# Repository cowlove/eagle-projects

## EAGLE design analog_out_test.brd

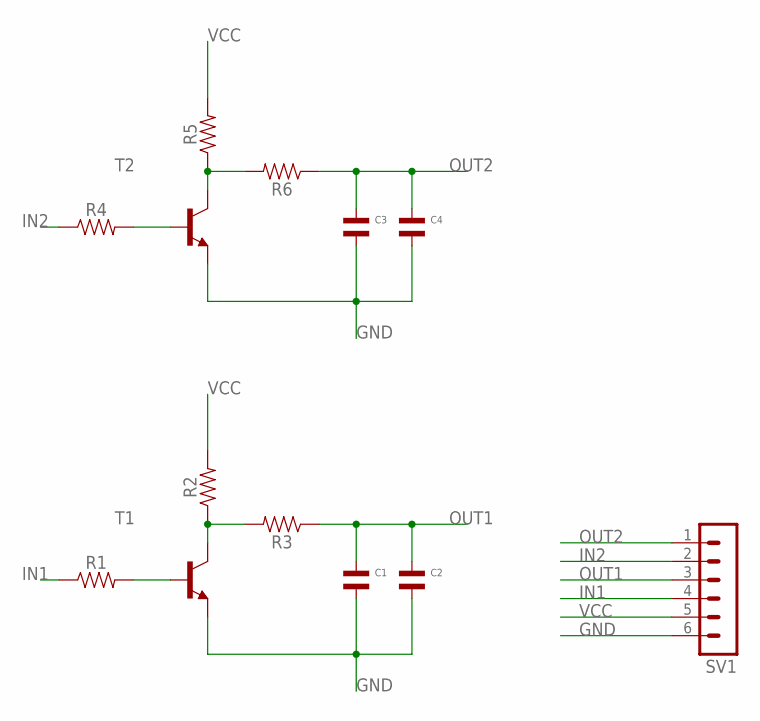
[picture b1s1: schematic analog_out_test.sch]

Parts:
C1, C2, C3, C4: CAPACITOR_NP_1206; C1206
R1, R2, R3, R4, R5, R6: 1206
SV1: MA06-1
T1, T2: BC849-NPN-SOT23-BEC; SOT23-BEC

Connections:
GND: C1.P$2, C2.P$2, C3.P$2, C4.P$2, SV1.6, T1.E, T2.E
IN1: R1.1, SV1.4
IN2: R4.1, SV1.2
unnamed: R2.1, R3.2, T1.C
unnamed: R1.2, T1.B
unnamed: R4.2, T2.B
unnamed: R5.1, R6.2, T2.C
OUT1: C1.P$1, C2.P$1, R3.1, SV1.3
OUT2: C3.P$1, C4.P$1, R6.1, SV1.1
VCC: R2.2, R5.2, SV1.5

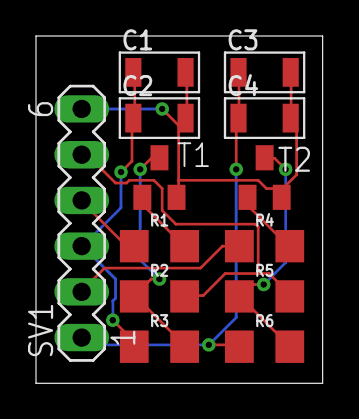
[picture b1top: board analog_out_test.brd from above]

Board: 2 copper layers, 15.9 x 19.3 mm, 13 parts (0 on the bottom side), 10 nets.

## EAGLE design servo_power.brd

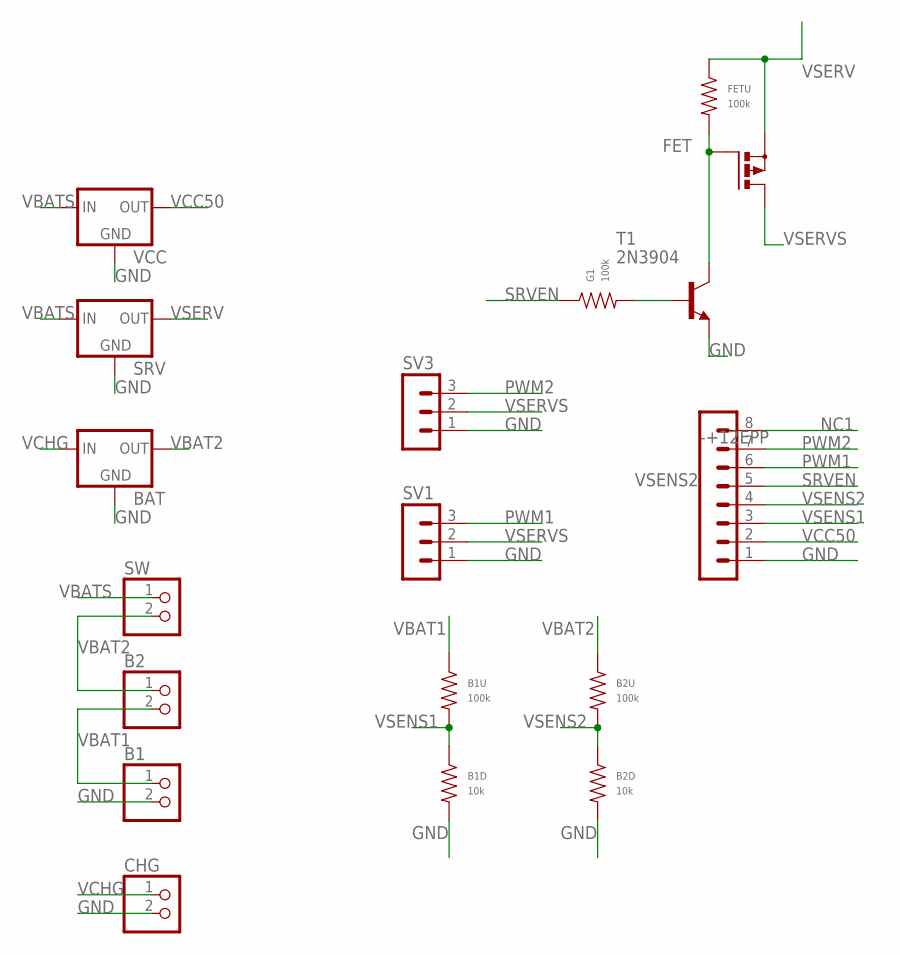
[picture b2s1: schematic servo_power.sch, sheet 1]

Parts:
-+12EPP: MA08-1
B1, B2: PINHD-1X2; 1X02
B1D, B2D: 10k; R1206
B1U, B2U: 100k; R1206
BAT: 78XXS
CHG: PINHD-1X2; 1X02
FET: PMOSFET_PTO220BV; TO220BV
FETU: 100k; R1206
G1: 100k; R1206
SRV: 78XXS
SV1, SV3: MA03-1
SW: PINHD-1X2; 1X02
T1: 2N3904; TO92
VCC: 78XXS

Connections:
GND: -+12EPP.1, B1.2, B1D.P$2, B2D.P$2, BAT.GND, CHG.2, SRV.GND, SV1.1, SV3.1, T1.3 (E), VCC.GND
unnamed: G1.P$2, T1.2 (B)
unnamed: FET.G, FETU.P$2, T1.1 (C)
NC1: -+12EPP.8
PWM1: -+12EPP.6, SV1.3
PWM2: -+12EPP.7, SV3.3
SRVEN: -+12EPP.5, G1.P$1
VBAT1: B1.1, B1U.P$1, B2.2
VBAT2: B2.1, B2U.P$1, BAT.OUT, SW.2
VBATS: SRV.IN, SW.1, VCC.IN
VCC50: -+12EPP.2, VCC.OUT
VCHG: BAT.IN, CHG.1
VSENS1: -+12EPP.3, B1D.P$1, B1U.P$2
VSENS2: -+12EPP.4, B2D.P$1, B2U.P$2
VSERV: FET.S, FETU.P$1, SRV.OUT
VSERVS: FET.D, SV1.2, SV3.2

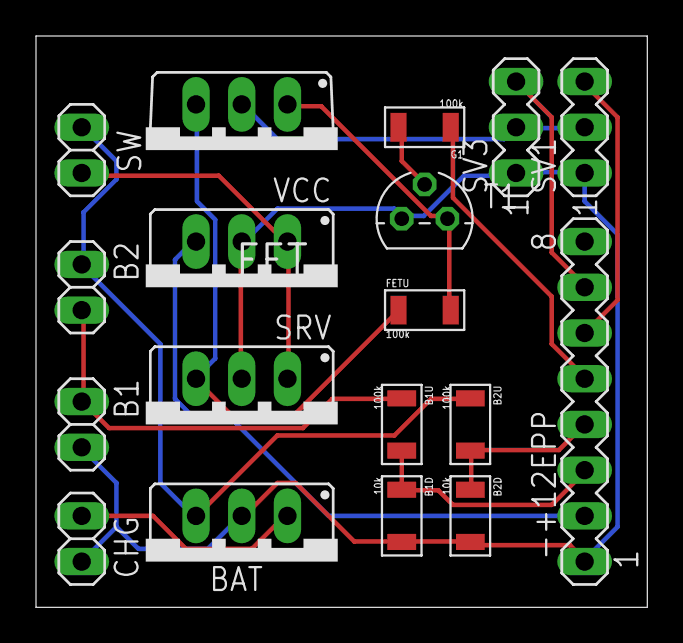
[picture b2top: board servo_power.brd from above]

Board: 2 copper layers, 34.0 x 31.7 mm, 18 parts (0 on the bottom side), 15 nets.

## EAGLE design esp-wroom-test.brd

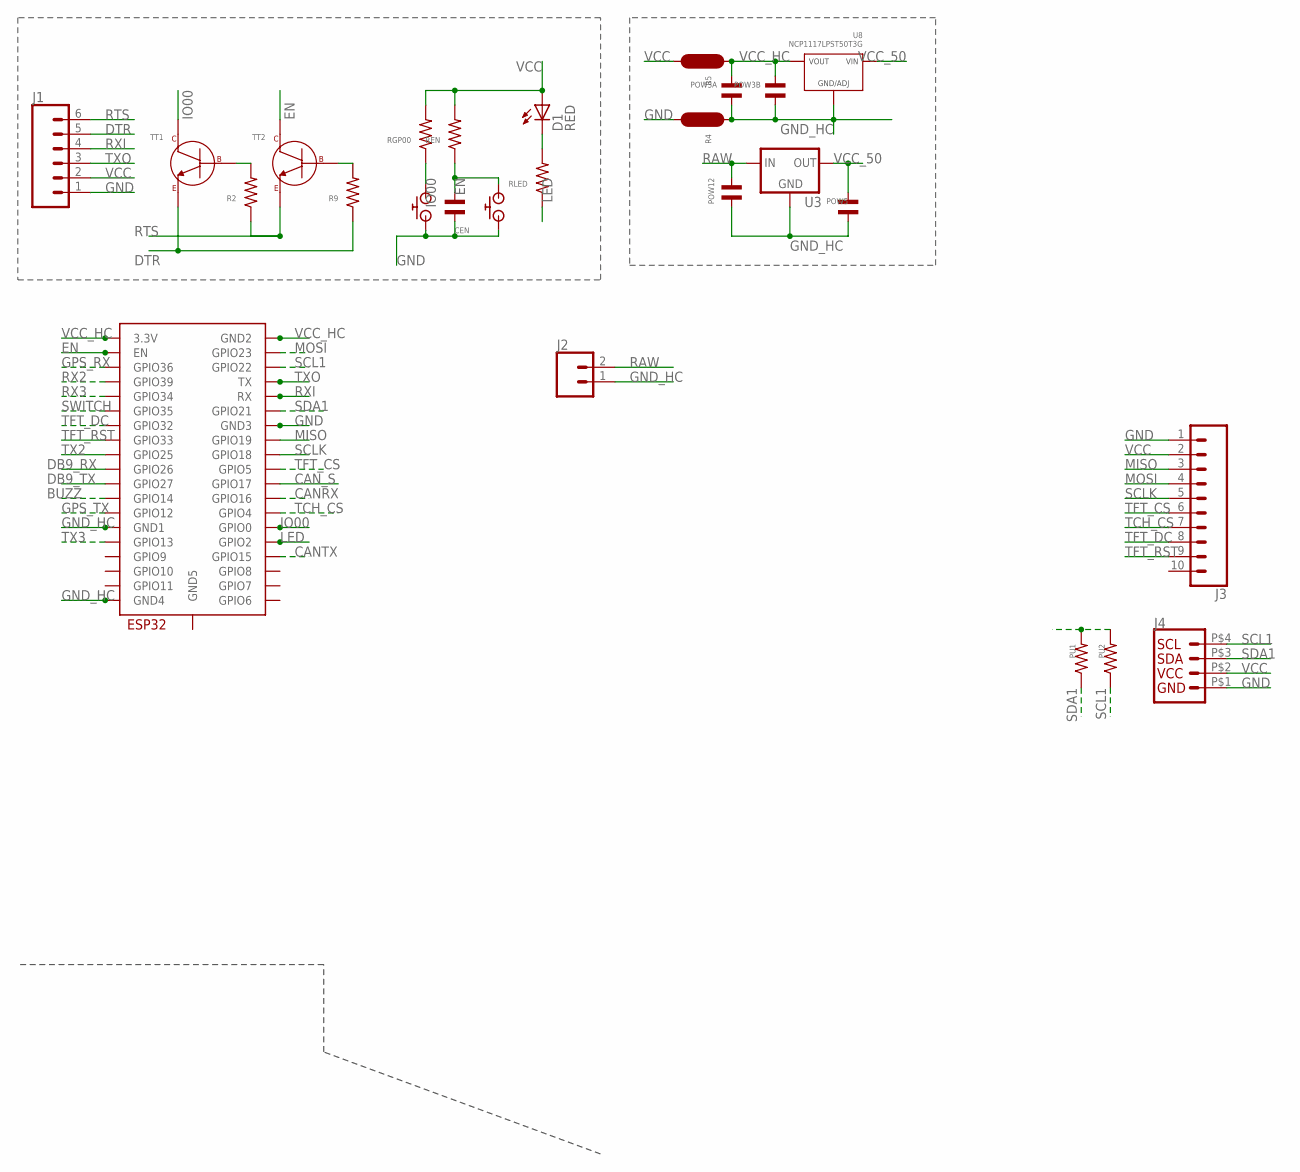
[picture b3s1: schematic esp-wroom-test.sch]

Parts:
CEN: CAPACITOR_NP_1206; C1206
D1: RED; LED-1206
J1: CONN_06; 1X6-1.25MM-SMD
J2: CONN_02; 1X02
J3: CONN_10; 1X10-1.25MM
J4: Vertical Qwiic Connector; JST04_1MM_HOLES
POW3A, POW3B, POW5, POW12: CAPACITOR_NP_1206; C1206
PU1, PU2: RESISTOR_1206; R1206
R2, R9: RESISTOR_1206; R1206
R4, R5: JUMPER; R0603_JMP
REN: RESISTOR_1206; R1206
RGP00: RESISTOR_1206; R1206
RLED: RESISTOR_1206; R1206
SW1, SW2: AMAZON_BUTTONB2010; C2010
TT1, TT2: MF-DSC-SOT233-MMBT3904; SOT-23-3
U3: V_REG_78XXSINK; TO220-IGO
U8: NCP1117LPST50T3G; SOT-223-3
U$3: ESP32-WROOM

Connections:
BUZZ: U$3.IO14 (GPIO14)
CANRX: U$3.IO16 (GPIO16)
CANTX: U$3.IO15 (GPIO15)
CAN_S: U$3.IO17 (GPIO17)
DB9_RX: U$3.IO26 (GPIO26)
DB9_TX: U$3.IO27 (GPIO27)
DTR: J1.5, R9.P$1, TT1.P$2 (EMITTER)
EN: CEN.P$1, REN.P$1, SW1.P$1, TT2.P$3 (COLLECTOR), U$3.EN
GND: CEN.P$2, J1.1, J3.1, J4.P$1 (1), R4.P$2, SW1.P$2, SW2.P$2, U$3.GND3
GND_HC: J2.1, POW3A.P$2, POW3B.P$2, POW5.P$2, POW12.P$2, R4.P$1, U3.GND, U8.P$2 (GND/ADJ), U$3.GND1, U$3.GND4
GPS_RX: U$3.SENSOR_VP (GPIO36)
GPS_TX: U$3.IO12 (GPIO12)
IO00: RGP00.P$1, SW2.P$1, TT1.P$3 (COLLECTOR), U$3.IO0 (GPIO0)
LED: RLED.P$1, U$3.IO2 (GPIO2)
MISO: J3.3, U$3.IO19 (GPIO19)
MOSI: J3.4, U$3.IO23 (GPIO23)
unnamed: D1.C, RLED.P$2
unnamed: R2.P$2, TT1.P$1 (BASE)
unnamed: R9.P$2, TT2.P$1 (BASE)
RAW: J2.2, POW12.P$1, U3.IN
RTS: J1.6, R2.P$1, TT2.P$2 (EMITTER)
RX2: U$3.SENSOR_VN (GPIO39)
RX3: U$3.IO34 (GPIO34)
RXI: J1.4, U$3.RX
SCL1: J4.P$4 (4), PU2.P$1, U$3.IO22 (GPIO22)
SCLK: J3.5, U$3.IO18 (GPIO18)
SDA1: J4.P$3 (3), PU1.P$1, U$3.IO21 (GPIO21)
SWITCH: U$3.IO35 (GPIO35)
TCH_CS: J3.7, U$3.IO4 (GPIO4)
TFT_CS: J3.6, U$3.IO5 (GPIO5)
TFT_DC: J3.8, U$3.IO32 (GPIO32)
TFT_RST: J3.9, U$3.IO33 (GPIO33)
TX2: U$3.IO25 (GPIO25)
TX3: U$3.IO13 (GPIO13)
TXO: J1.3, U$3.TX
VCC: D1.A, J1.2, J3.2, J4.P$2 (2), PU1.P$2, PU2.P$2, R5.P$2, REN.P$2, RGP00.P$2
VCC_50: POW5.P$1, U3.OUT, U8.P$4 (VIN)
VCC_HC: POW3A.P$1, POW3B.P$1, R5.P$1, U8.P$1 (VOUT), U8.P$3 (VOUT), U$3.3V3 (3.3V), U$3.GND2

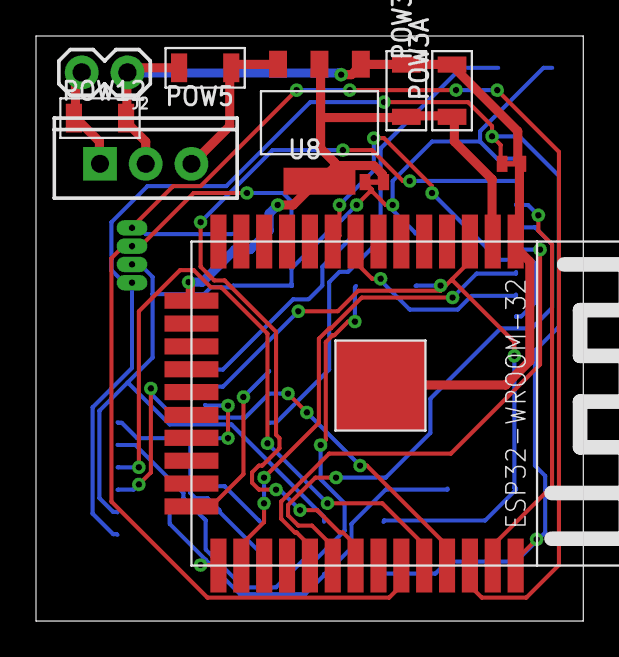
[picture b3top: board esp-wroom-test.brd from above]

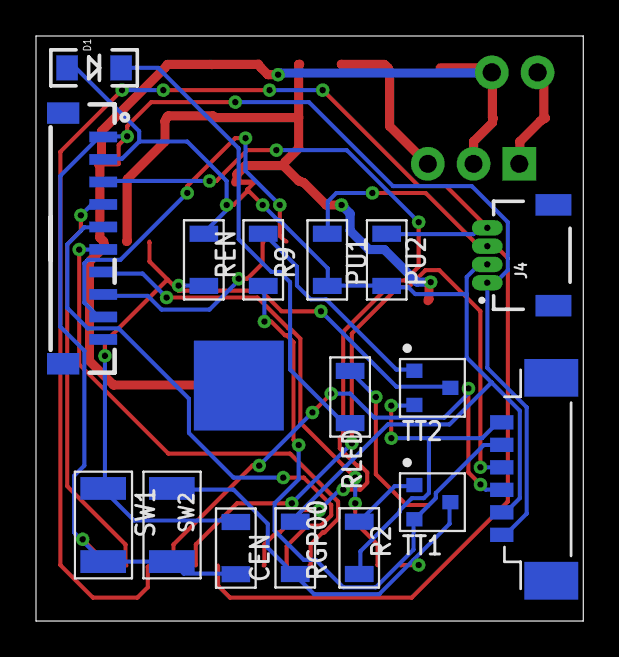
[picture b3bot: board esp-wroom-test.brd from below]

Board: 2 copper layers, 30.4 x 32.5 mm, 26 parts (16 on the bottom side), 25 nets.

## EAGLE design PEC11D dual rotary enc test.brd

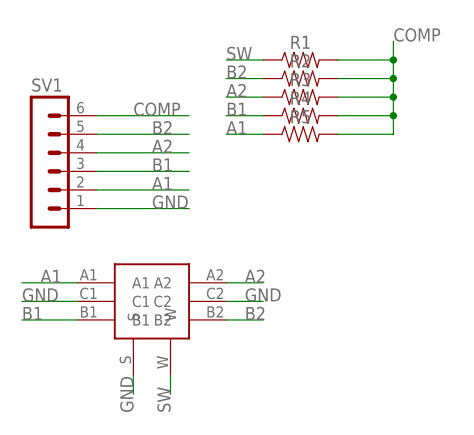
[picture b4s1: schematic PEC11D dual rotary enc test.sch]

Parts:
R1, R2, R3, R4, R5: 1206
SV1: MA06-1
U$1: PEC11DPEC11D; PEC11D_TH

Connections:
A1: R5.1, SV1.2, U$1.A1
A2: R3.1, SV1.4, U$1.A2
B1: R4.1, SV1.3, U$1.B1
B2: R2.1, SV1.5, U$1.B2
COMP: R1.2, R2.2, R3.2, R4.2, R5.2, SV1.6
GND: SV1.1, U$1.C1, U$1.C2, U$1.S
SW: R1.1, U$1.W

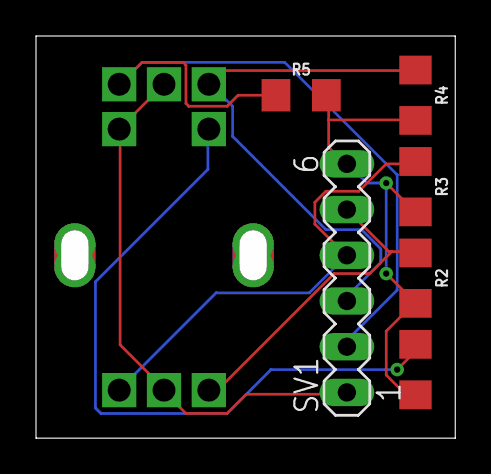
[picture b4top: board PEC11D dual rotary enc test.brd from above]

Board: 2 copper layers, 21.8 x 20.8 mm, 7 parts (0 on the bottom side), 7 nets.

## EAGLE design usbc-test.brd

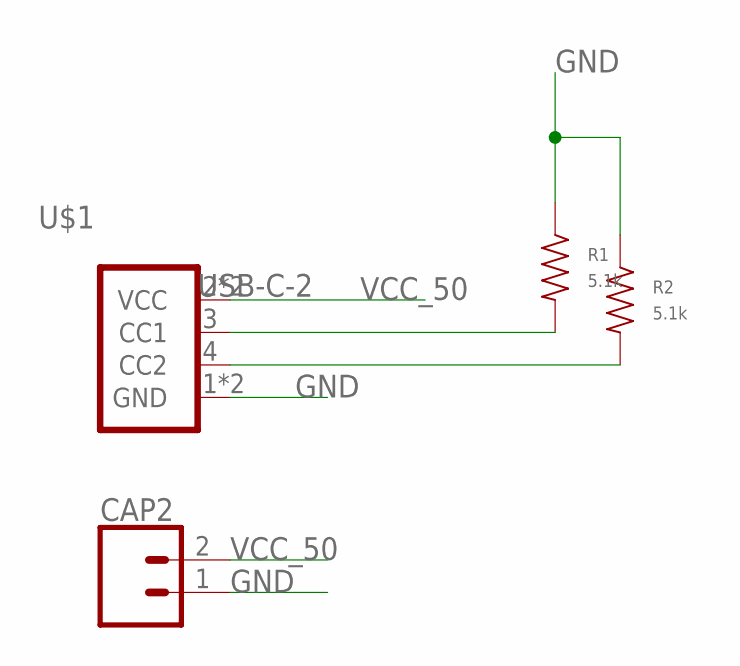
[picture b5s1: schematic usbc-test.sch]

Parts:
CAP2: CONN_02; 1X02
R1, R2: 5.1k; R0603
U$1: USB-C-2; USB-C-16

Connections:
GND: CAP2.1, R1.P$1, R2.P$1, U$1.1 (GND), U$1.6 (GND)
unnamed: R1.P$2, U$1.3 (CC1)
unnamed: R2.P$2, U$1.4 (CC2)
VCC_50: CAP2.2, U$1.2 (VCC), U$1.5 (VCC)

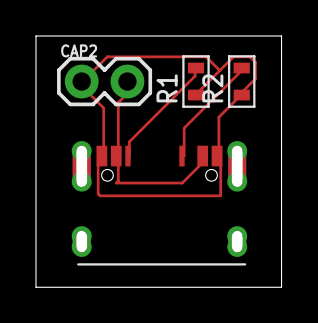
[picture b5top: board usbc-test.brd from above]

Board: 2 copper layers, 13.0 x 13.4 mm, 4 parts (0 on the bottom side), 4 nets.

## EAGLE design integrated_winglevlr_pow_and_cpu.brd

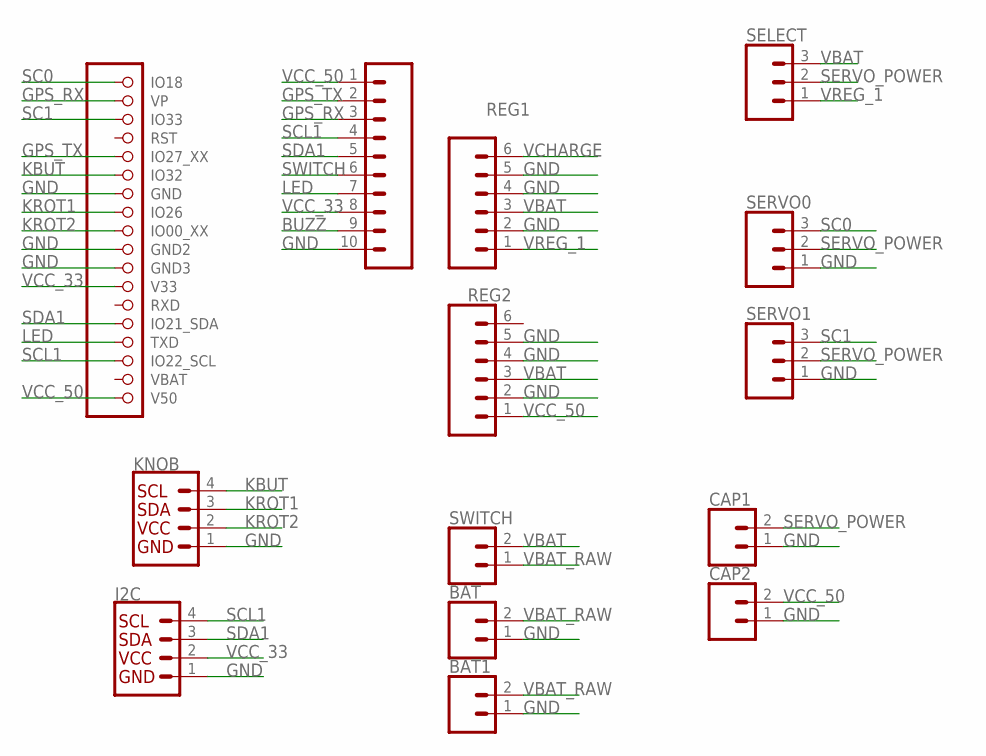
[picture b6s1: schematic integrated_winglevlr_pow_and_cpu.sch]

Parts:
BAT, BAT1: CONN_02; 1X02
CAP1, CAP2: CONN_02; 1X02
I2C: Vertical Qwiic Connector; JST04_1MM_VERT
J2: CONN_10; 1X10-1.25MM
JP1: 000_ESP32_D1MINI; 00_2X9
KNOB: Vertical Qwiic Connector; JST04_1MM_VERT
REG1, REG2: CONN_06SILK_FEMALE_PTH; 1X06
SELECT: 455-1750-1-ND; 1X03
SERVO0, SERVO1: 455-1750-1-ND; 1X03
SWITCH: CONN_02; 1X02

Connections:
BUZZ: J2.9
GND: BAT.1, BAT1.1, CAP1.1, CAP2.1, I2C.1, J2.10, JP1.7 (GND), JP1.10 (GND2), JP1.11 (GND3), KNOB.1, REG1.2, REG1.4, REG1.5, REG2.2, REG2.4, REG2.5, SERVO0.1, SERVO1.1
GPS_RX: J2.3, JP1.2 (VP)
GPS_TX: J2.2, JP1.5 (IO27_XX)
KBUT: JP1.6 (IO32), KNOB.4
KROT1: JP1.8 (IO26), KNOB.3
KROT2: JP1.9 (IO00_XX), KNOB.2
LED: J2.7, JP1.15 (TXD)
SC0: JP1.1 (IO18), SERVO0.3
SC1: JP1.3 (IO33), SERVO1.3
SCL1: I2C.4, J2.4, JP1.16 (IO22_SCL)
SDA1: I2C.3, J2.5, JP1.14 (IO21_SDA)
SERVO_POWER: CAP1.2, SELECT.2, SERVO0.2, SERVO1.2
SWITCH: J2.6
VBAT: REG1.3, REG2.3, SELECT.3, SWITCH.2
VBAT_RAW: BAT.2, BAT1.2, SWITCH.1
VCC_33: I2C.2, J2.8, JP1.12 (V33)
VCC_50: CAP2.2, J2.1, JP1.18 (V50), REG2.1
VCHARGE: REG1.6
VREG_1: REG1.1, SELECT.1

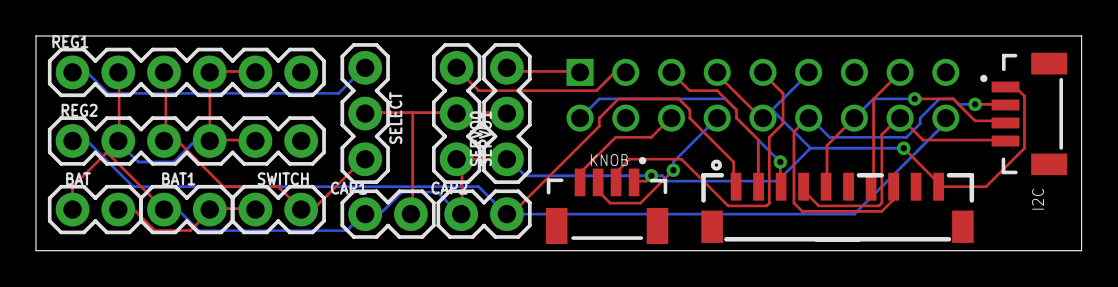
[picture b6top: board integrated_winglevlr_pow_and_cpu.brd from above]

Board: 2 copper layers, 58.1 x 11.9 mm, 14 parts (1 on the bottom side), 17 nets.

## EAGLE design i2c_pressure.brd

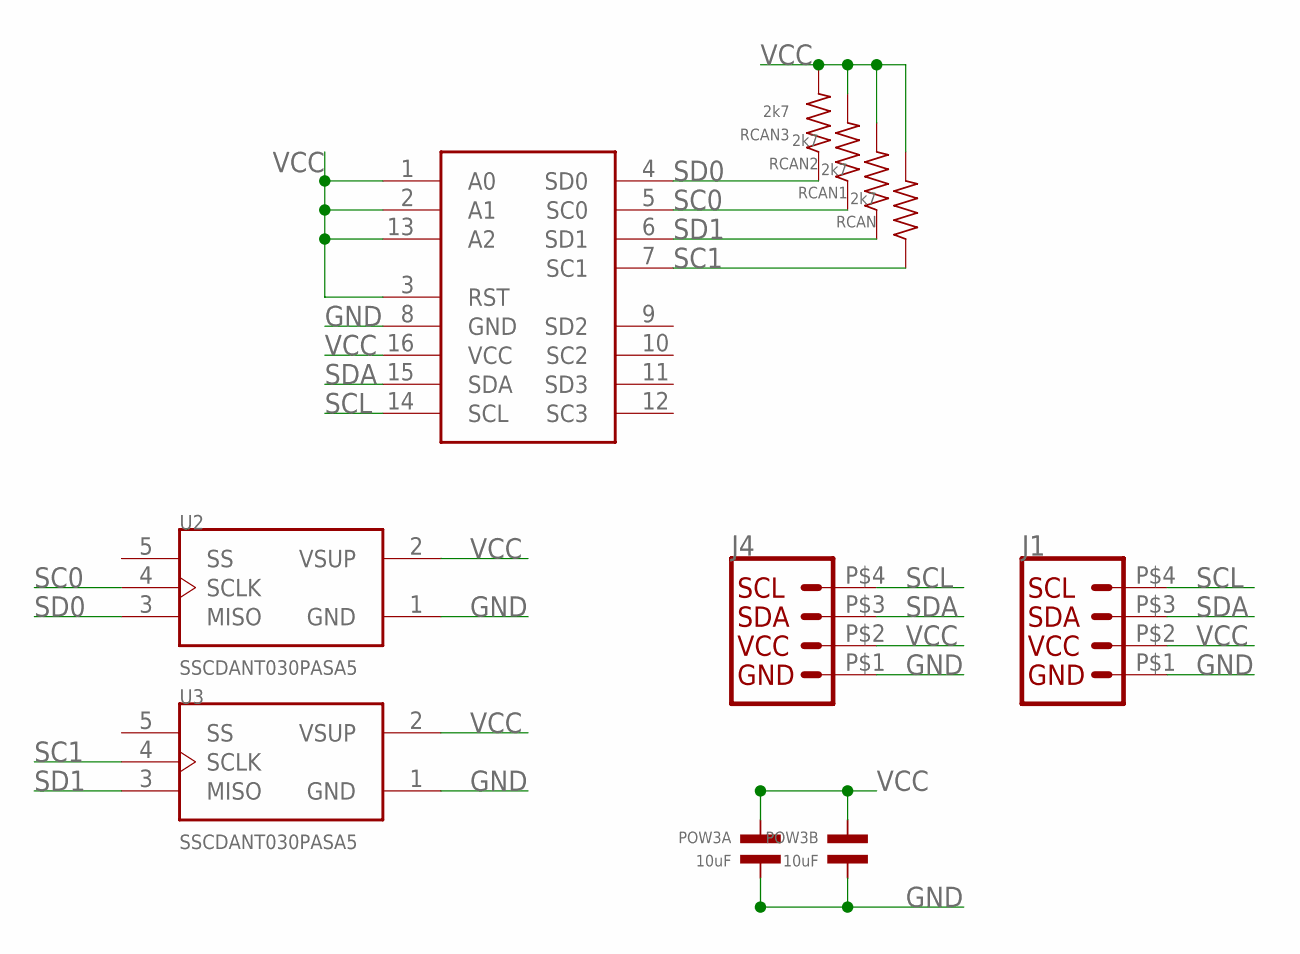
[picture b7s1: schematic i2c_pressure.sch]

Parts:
J1, J4: Vertical Qwiic Connector; JST04_1MM_HOLES
POW3A, POW3B: 10uF; C0603
RCAN, RCAN1, RCAN2, RCAN3: 2k7; R0603
U2, U3: SSCDANT030PASA5; XDCR_SSCDANT030PASA5
U$1: TCA9546ATSSOP16; TSSOP16

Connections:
GND: J1.P$1 (1), J4.P$1 (1), POW3A.P$2, POW3B.P$2, U2.1 (GND), U3.1 (GND), U$1.8 (GND)
SC0: RCAN2.P$1, U2.4 (SCLK), U$1.5 (SC0)
SC1: RCAN.P$1, U3.4 (SCLK), U$1.7 (SC1)
SCL: J1.P$4 (4), J4.P$4 (4), U$1.14 (SCL)
SD0: RCAN3.P$1, U2.3 (MISO), U$1.4 (SD0)
SD1: RCAN1.P$1, U3.3 (MISO), U$1.6 (SD1)
SDA: J1.P$3 (3), J4.P$3 (3), U$1.15 (SDA)
VCC: J1.P$2 (2), J4.P$2 (2), POW3A.P$1, POW3B.P$1, RCAN.P$2, RCAN1.P$2, RCAN2.P$2, RCAN3.P$2, U2.2 (VSUP), U3.2 (VSUP), U$1.1 (A0), U$1.2 (A1), U$1.3 (RST), U$1.13 (A2), U$1.16 (VCC)

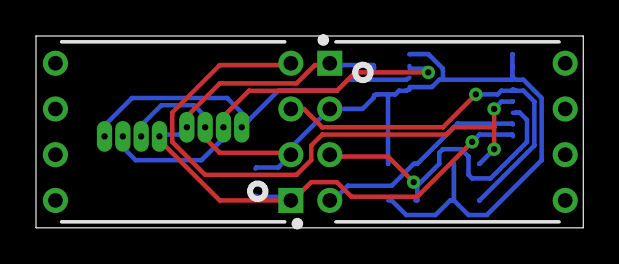
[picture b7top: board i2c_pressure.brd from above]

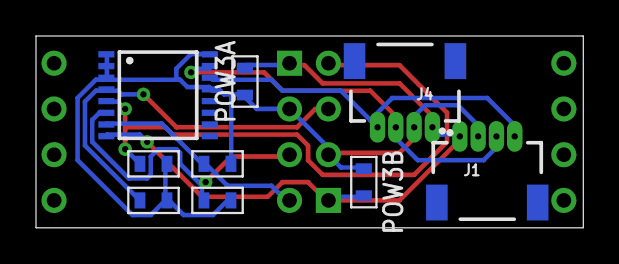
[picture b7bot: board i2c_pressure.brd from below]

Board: 2 copper layers, 30.4 x 10.7 mm, 11 parts (9 on the bottom side), 8 nets.

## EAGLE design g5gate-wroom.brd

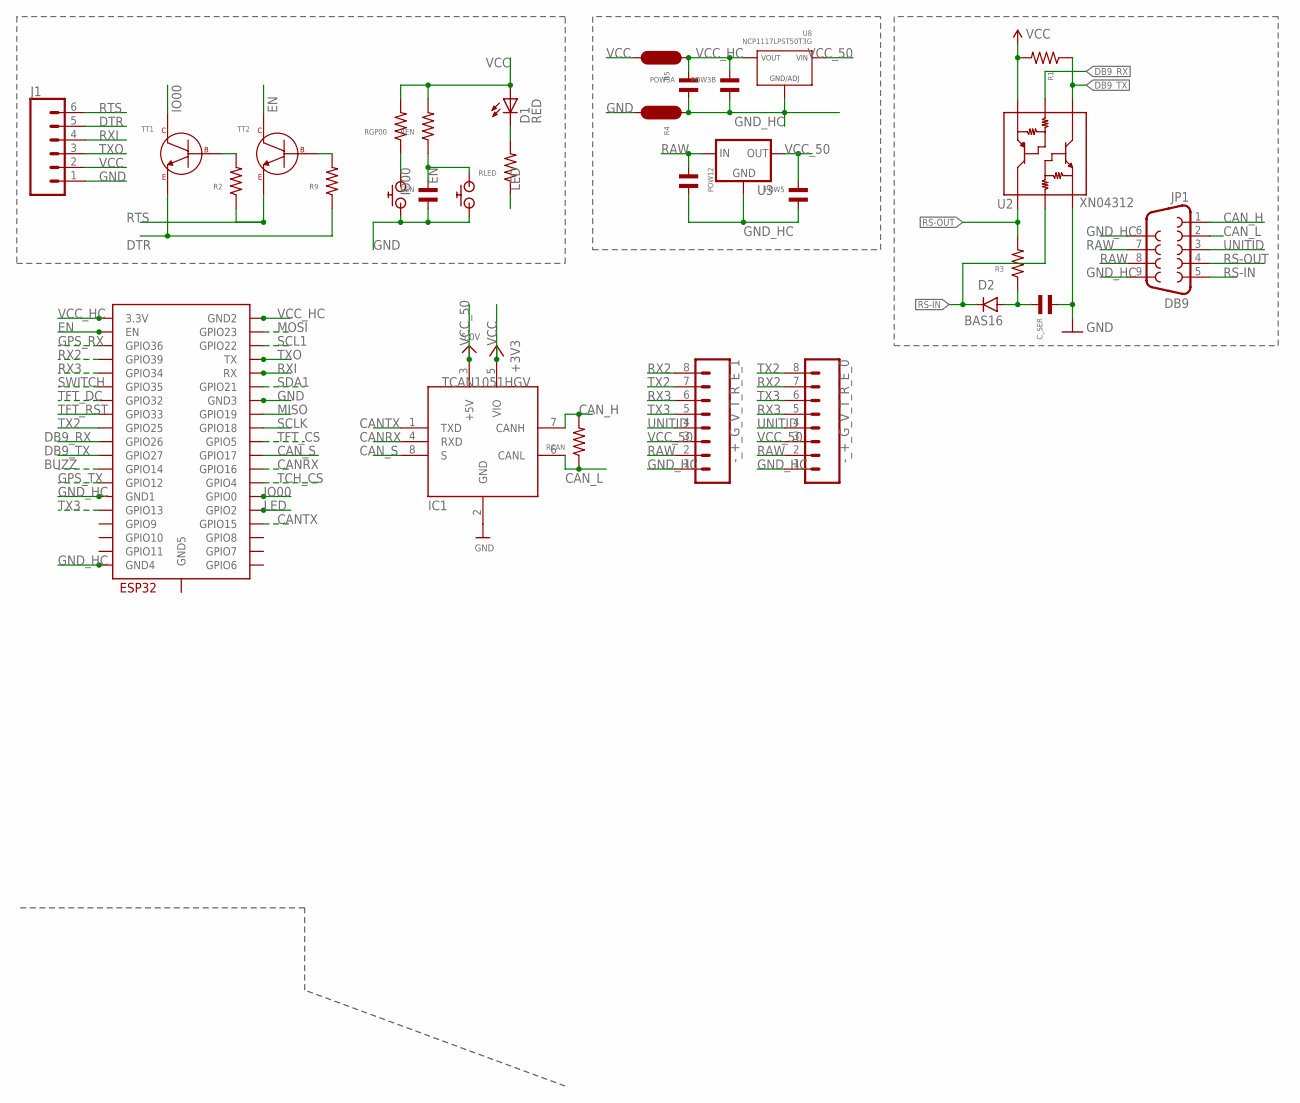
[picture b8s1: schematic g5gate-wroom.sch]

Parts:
-_+_G_V_T_R_E_0, -_+_G_V_T_R_E_1: MF-CON-2.54mm-01x08; 1X08
CEN: CAPACITOR_NP_0603; C0603
C_SER: CAPACITOR_NP_0603; C0603
D1: RED; LED-0603
D2: BAS16; SOD-323
IC1: TCAN1051HGV; SOIC8_150MIL
J1: CONN_06; 1X6-1.25MM-SMD
JP1: DB9
POW3A, POW3B, POW5, POW12: CAPACITOR_NP_0603; C0603
R1, R2, R3, R9: RESISTOR_0603; R0603
R4, R5: JUMPER; R0603_JMP
RCAN: RESISTOR_0603; R0603
REN: RESISTOR_0603; R0603
RGP00: RESISTOR_0603; R0603
RLED: RESISTOR_0603; R0603
TT1, TT2: MF-DSC-SOT233-MMBT3904; SOT-23-3
U2: XN04312; SOT23-6
U3: V_REG_78XXSINK; TO220-IGO
U8: NCP1117LPST50T3G; SOT-223-3
U$1, U$2: AMAZON_BUTTONB2010; C2010
U$3: ESP32-WROOM

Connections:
BUZZ: U$3.IO14 (GPIO14)
CANRX: IC1.4 (RXD), U$3.IO16 (GPIO16)
CANTX: IC1.1 (TXD), U$3.IO15 (GPIO15)
CAN_H: IC1.7 (CANH), JP1.1, RCAN.P$2
CAN_L: IC1.6 (CANL), JP1.2, RCAN.P$1
CAN_S: IC1.8 (S), U$3.IO17 (GPIO17)
DB9_RX: U2.2 (B2), U$3.IO26 (GPIO26)
DB9_TX: R1.P$1, U2.1 (C1), U$3.IO27 (GPIO27)
DTR: J1.5, R9.P$1, TT1.P$2 (EMITTER)
EN: CEN.P$1, REN.P$1, TT2.P$3 (COLLECTOR), U$2.P$1, U$3.EN
GND: CEN.P$2, C_SER.P$2, IC1.2 (GND), J1.1, R4.P$2, U2.6 (E1), U$1.P$2, U$2.P$2, U$3.GND3
GND_HC: -_+_G_V_T_R_E_0.1, -_+_G_V_T_R_E_1.1, JP1.6, JP1.9, POW3A.P$2, POW3B.P$2, POW5.P$2, POW12.P$2, R4.P$1, U3.GND, U8.P$2 (GND/ADJ), U$3.GND1, U$3.GND4
GPS_RX: U$3.SENSOR_VP (GPIO36)
GPS_TX: U$3.IO12 (GPIO12)
IO00: RGP00.P$1, TT1.P$3 (COLLECTOR), U$1.P$1, U$3.IO0 (GPIO0)
LED: RLED.P$1, U$3.IO2 (GPIO2)
MISO: U$3.IO19 (GPIO19)
MOSI: U$3.IO23 (GPIO23)
unnamed: D1.C, RLED.P$2
unnamed: R2.P$2, TT1.P$1 (BASE)
unnamed: C_SER.P$1, D2.A, R3.P$1
unnamed: R9.P$2, TT2.P$1 (BASE)
RAW: -_+_G_V_T_R_E_0.2, -_+_G_V_T_R_E_1.2, JP1.7, JP1.8, POW12.P$1, U3.IN
RS-IN: D2.C, JP1.5, U2.5 (B1)
RS-OUT: JP1.4, R3.P$2, U2.4 (C2)
RTS: J1.6, R2.P$1, TT2.P$2 (EMITTER)
RX2: -_+_G_V_T_R_E_0.7, -_+_G_V_T_R_E_1.8, U$3.SENSOR_VN (GPIO39)
RX3: -_+_G_V_T_R_E_0.5, -_+_G_V_T_R_E_1.6, U$3.IO34 (GPIO34)
RXI: J1.4, U$3.RX
SCL1: U$3.IO22 (GPIO22)
SCLK: U$3.IO18 (GPIO18)
SDA1: U$3.IO21 (GPIO21)
SWITCH: U$3.IO35 (GPIO35)
TCH_CS: U$3.IO4 (GPIO4)
TFT_CS: U$3.IO5 (GPIO5)
TFT_DC: U$3.IO32 (GPIO32)
TFT_RST: U$3.IO33 (GPIO33)
TX2: -_+_G_V_T_R_E_0.8, -_+_G_V_T_R_E_1.7, U$3.IO25 (GPIO25)
TX3: -_+_G_V_T_R_E_0.6, -_+_G_V_T_R_E_1.5, U$3.IO13 (GPIO13)
TXO: J1.3, U$3.TX
UNITID: -_+_G_V_T_R_E_0.4, -_+_G_V_T_R_E_1.4, JP1.3
VCC: D1.A, IC1.5 (VIO), J1.2, R1.P$2, R5.P$2, REN.P$2, RGP00.P$2, U2.3 (E2)
VCC_50: -_+_G_V_T_R_E_0.3, -_+_G_V_T_R_E_1.3, IC1.3 (+5V), POW5.P$1, U3.OUT, U8.P$4 (VIN)
VCC_HC: POW3A.P$1, POW3B.P$1, R5.P$1, U8.P$1 (VOUT), U8.P$3 (VOUT), U$3.3V3 (3.3V), U$3.GND2

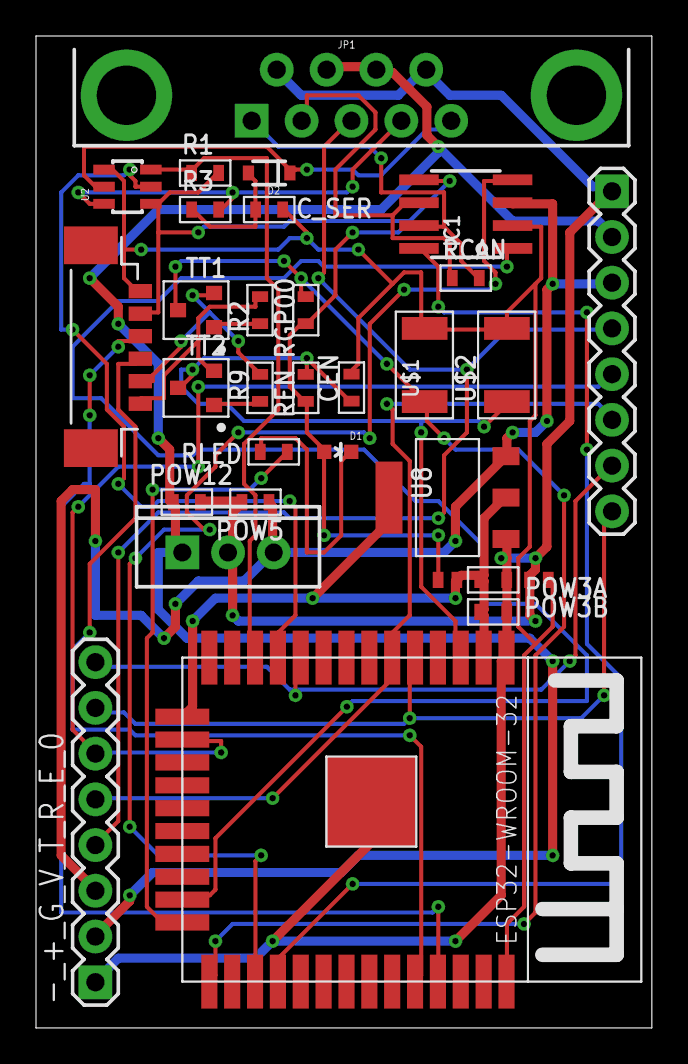
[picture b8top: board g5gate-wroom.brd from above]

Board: 2 copper layers, 34.2 x 55.1 mm, 31 parts (0 on the bottom side), 31 nets.

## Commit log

2021-03-03 Initial commit, TTGO-TS-dash-display ordered 3/2/2021, esp12e-test ordered 3/3
2021-03-04 Add button and STEMMA connectors to esp12e-test board
2021-03-06 Spin i2c_adc board, add jst connectors, 6 voltage divider channels
2021-03-16 First spin of TTGO to TFT mating board
2021-03-17 As ordered
2021-03-18 Added more trinkets to TFT touch boards
2021-03-18 Fix IO16 bug, change to better stemma-st connector
2021-03-18 Initial commit of wroom test board, as ordered
2021-03-18 Added tented vias
2021-03-19 Tinkering with expected changes for dash-mount board
2021-04-08 Ordered again
2021-04-08 Fix board bug, order again
2021-04-08 Enlarged usb pin holes
2021-04-11 Steerstick power and jst test boards, as ordered
2021-04-12 px4 board
2021-04-12 move via
2021-04-12 move other via
2021-04-13 Goddamit jst throughole test wasn't throughhole
2021-04-18 Fix USB connector dimensions
2021-04-26 Narrow board, add esp32 reset mechanism
2021-04-26 Actually save
2021-05-02 add 01jim.lbr
2021-05-02 add 00jim.lbr
2021-05-02 break out g5gate into wroom and min132 variands
2021-05-05 introduce esp32 plus tft and gps 10pin connectors
2021-05-05 add library to gitgnore
2021-05-05 library changes
2021-05-05 Add touchscreen header directly to board
2021-05-05 forgot to jumper gnd and gnd_hc
2021-05-05 wroom test two sided
2021-05-06 pressure board needs i2c mux, introduce engmon-wroom
2021-05-06 add i2c multiplexer to 00jim and pressure board
2021-10-12 First integrated winglevlr board
2021-10-29 Add I2C connector
2021-11-11 Added USB C device and test project
2021-11-11 Add USBC diagram
2021-12-17 Some changes
2021-12-22 Add usbc
2021-12-22 Fix merge error in jim01.lbr
2022-11-25 Servo power board
2022-11-25 PEC11D rotary encoder test chip
2022-11-27 Change wroom test to 12-06 resistors/leds
2022-11-27 Add missing vcc gnd jumpers
2022-12-06 Increase wire size to 10mil

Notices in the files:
parts and their libraries:
SparkFun-Connectors: Licensing: CC v3.0 Share-Alike You are welcome to use this library for commercial purposes.
SparkFun-IC-Power: Licensing: Creative Commons ShareAlike 4.0 International - https://creativecommons.org/licenses/by-sa/4.0
